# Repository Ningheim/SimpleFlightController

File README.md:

# SimpleFlightController

This is a USB-C powered 2-layer flight controller built around the STM32F722. It's 2S LiPo/Li-ion battery, a 6-axis IMU, a barometer, microSD logging, and two servo outputs.

## List of Materials

- MCU: STM32F722RET6
- IMU: ICM-20948 (SPI) — barometer: BME280 (I2C)
- Charger: BQ25887
- Power: TPS63070 buck-boost, LMR51430 buck
- microSD: 4-bit SD card slot
- J1/J3: servo/PWM headers
- J2: 2S battery screw terminal
- SW1 reset, SW2 boot, D1 status LED indicator
- 25MHz HSE + 32.768kHz LSE crystals
- Board: 50x55mm, 2-layer, KiCad 
- the hardware folder has the KiCad files. Run lcsc.py first to get parts KiCAD didn't have. This came from the hack club guide.

## Power architecture

```
2S Battery ----> TPS63070 ----> VSYS ----> LMR51430 ----> 3.3V rail

USB-C VBUS ----> BQ25887 Charger
```

## How To Make It Yourself

1. Run `lcsc.py` so the libraries resolve.
2. Open the .kicad_pro file in KiCad.
3. Export gerbers/drill/pick-and-place and send to JLCPCB for a quote.
4. Generate a BOM and assemble with a stencil, paste, and reflow.
5. Power up: 2S LIPO pack on the battery pad, `J2`.
6. Flash: hold `SW2`, reset with `SW1`, flash over `USB1`.

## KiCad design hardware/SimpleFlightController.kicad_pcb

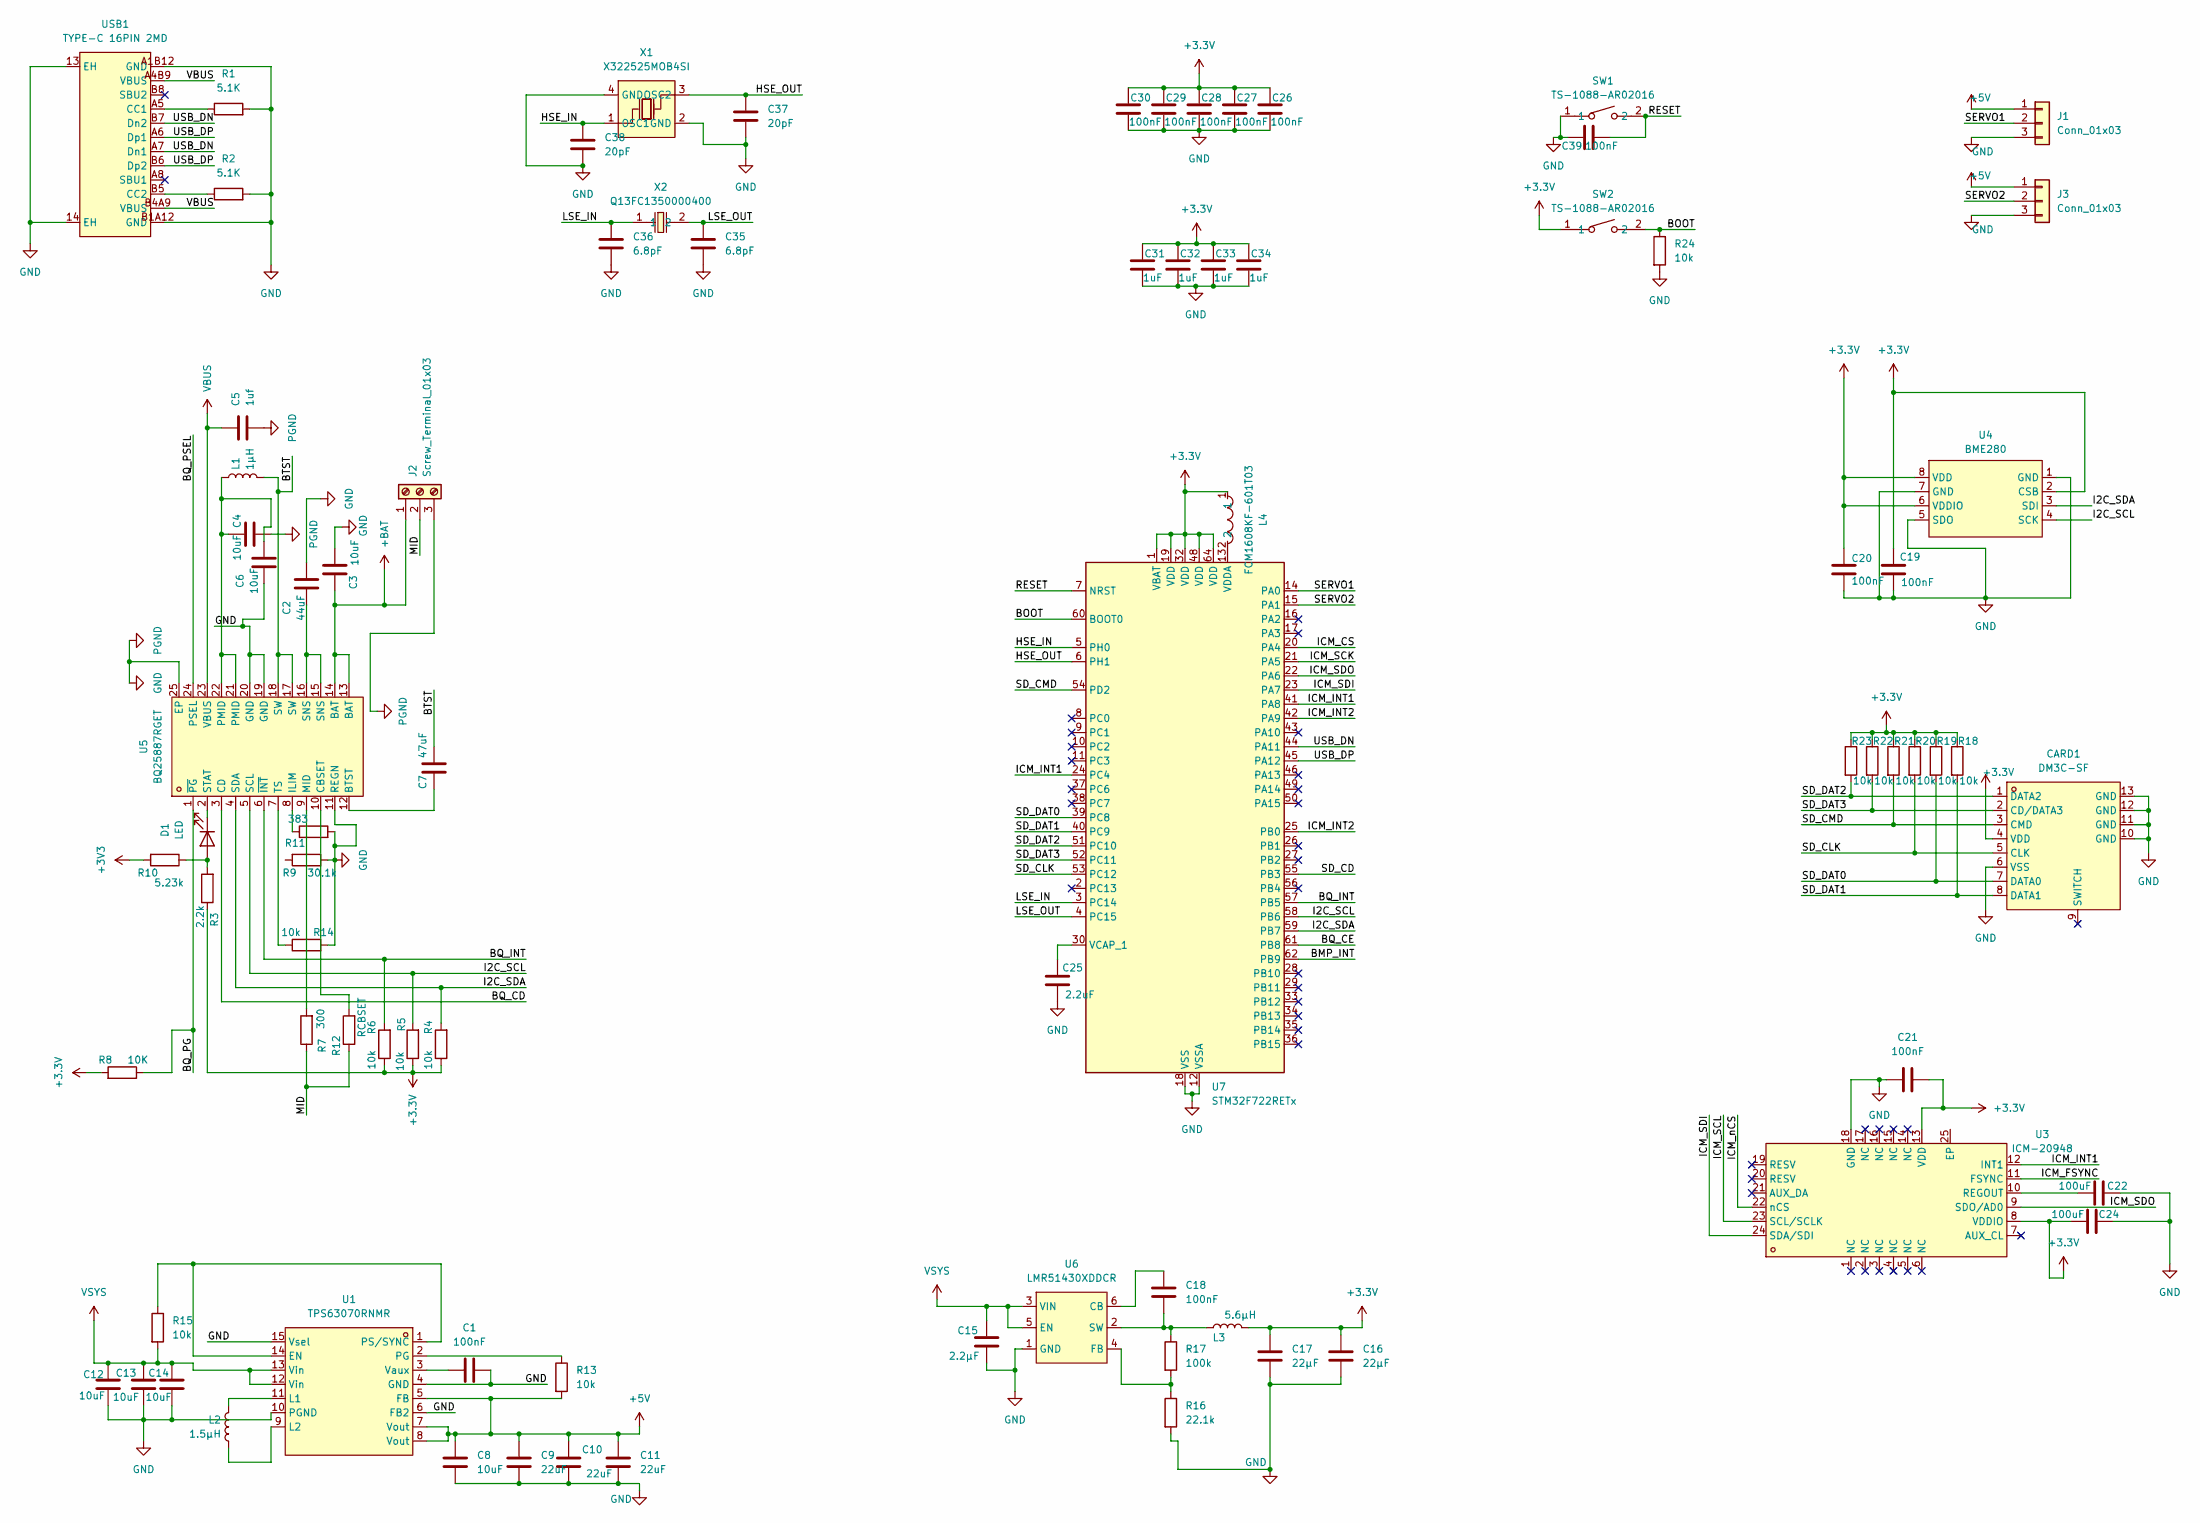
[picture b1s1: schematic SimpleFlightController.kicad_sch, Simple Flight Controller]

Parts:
C1, C18, C19, C20, C21, C26, C27, C28, C29, C30, C39: 100nF; C_0402_1005Metric
C2: 44uF; C_0805_2012Metric
C3, C4, C6, C8, C12, C13, C14: 10uF; C_0402_1005Metric
C5: 1uf; C_0402_1005Metric
C7: 47uF; C_0805_2012Metric
C9, C10, C11: 22uF; C_0805_2012Metric
C15: 2.2μF; C_0402_1005Metric
C16, C17: 22μF; C_0805_2012Metric
C22, C24: 100uF; C_0402_1005Metric
C25: 2.2uF; C_0402_1005Metric
C31, C32, C33, C34: 1uF; C_0402_1005Metric
C35, C36: 6.8pF; C_0402_1005Metric
C37, C38: 20pF; C_0402_1005Metric
CARD1: DM3C-SF; TF-SMD_DM3CS-SF; MPN DM3C-SF; LCSC Part C3177034
D1: LED; LED_0402_1005Metric
J1, J3: Conn_01x03; PinHeader_2x03_P2.54mm_Vertical
J2: Screw_Terminal_01x03; TerminalBlock_Xinya_XY308-2.54-3P_1x03_P2.54mm_Horizontal
L1: 1μH; L_1008_2520Metric
L2: 1.5μH; L_APV_ANR4012
L3: 5.6μH; L_1210_3225Metric
L4: FCM1608KF-601T03; L0603; MPN FCM1608KF-601T03; LCSC Part C141723
R1, R2: 5.1K; R_0201_0603Metric
R3: 2.2k; R_0201_0603Metric
R4, R5, R6, R13, R14, R15, R18, R19, R20, R21, R22, R23, R24: 10k; R_0201_0603Metric
R7: 300; R_0201_0603Metric
R8: 10K; R_0201_0603Metric
R9: 30.1k; R_0201_0603Metric
R10: 5.23k; R_0201_0603Metric
R11: 383; R_0201_0603Metric
R12: RCBSET; R_0201_0603Metric
R16: 22.1k; R_0201_0603Metric
R17: 100k; R_0201_0603Metric
SW1, SW2: TS-1088-AR02016; SW-SMD_L3.9-W3.0-P4.45; MPN TS-1088-AR02016; LCSC Part C720477
U1: TPS63070RNMR; VQFN-15_L3.0-W2.5-P0.50-BL; MPN TPS63070RNMR; LCSC Part C109322
U3: ICM-20948; QFN-24_L3.0-W3.0-P0.40-BL-EP; MPN ICM-20948; LCSC Part C726001
U4: BME280; LGA-8_BME280_BL; MPN BME280; LCSC Part C92489
U5: BQ25887RGET; VQFN-24_L4.0-W4.0-P0.50-TL-EP2.7; MPN BQ25887RGET; LCSC Part C2862617
U6: LMR51430XDDCR; SOT-23-6_L2.9-W1.6-P0.95-LS2.8-BL; MPN LMR51430XDDCR; LCSC Part C5185863
U7: STM32F722RETx; LQFP-64_10x10mm_P0.5mm
USB1: TYPE-C 16PIN 2MD; USB-C-SMD_TYPE-C-16PIN-2MD-073; MPN TYPE-C 16PIN 2MD(073); LCSC Part C2765186
X1: X322525MOB4SI; CRYSTAL-SMD_4P-L3.2-W2.5-BL; MPN X322525MOB4SI; LCSC Part C9006
X2: Q13FC1350000400; FC-135R_L3.2-W1.5; MPN Q13FC13500004; LCSC Part C32346

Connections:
+3.3V: C16.1, C17.1, C19.1, C20.1, C21.2, C24.1, C26.1, C27.1, C28.1, C29.1, C30.1, C31.1, C32.1, C33.1, C34.1, CARD1.4 (VDD), L3.2, L4.1, R3.1, R4.1, R5.1, R6.1, R8.2, R18.1, R19.1, R20.1, R21.1, R22.1, R23.1, SW2.1, U3.8 (VDDIO), U3.13 (VDD), U4.2 (CSB), U4.6 (VDDIO), U4.8 (VDD), U7.1 (VBAT), U7.19 (VDD), U7.32 (VDD), U7.48 (VDD), U7.64 (VDD)
+3V3: R10.2
+5V: C8.1, C9.1, C10.1, C11.1, J1.1, J3.1, R13.2, U1.5 (FB), U1.7 (Vout), U1.8 (Vout)
+BAT: C3.1, J2.1, U5.13 (BAT), U5.14 (BAT)
/BMP_INT: U7.62 (PB9)
/BOOT: R24.1, SW2.2, U7.60 (BOOT0)
/BQ_CD: U5.3 (CD)
/BQ_CE: U7.61 (PB8)
/BQ_INT: R6.2, U5.6 (~INT), U7.57 (PB5)
/BQ_PG: R8.1, U5.1 (~PG)
/BQ_PSEL: U5.24 (PSEL)
/BTST: C7.2, L1.2, U5.17 (SW), U5.18 (SW)
/HSE_IN: C38.1, U7.5 (PH0), X1.1 (OSC1)
/HSE_OUT: C37.1, U7.6 (PH1), X1.3 (OSC2)
/I2C_SCL: R5.2, U4.4 (SCK), U5.5 (SCL), U7.58 (PB6)
/I2C_SDA: R4.2, U4.3 (SDI), U5.4 (SDA), U7.59 (PB7)
/ICM_CS: U7.20 (PA4)
/ICM_FSYNC: U3.11 (FSYNC)
/ICM_INT1: U3.12 (INT1), U7.24 (PC4), U7.41 (PA8)
/ICM_INT2: U7.25 (PB0), U7.42 (PA9)
/ICM_SCK: U7.21 (PA5)
/ICM_SCL: U3.23 (SCL/SCLK)
/ICM_SDI: U3.24 (SDA/SDI), U7.23 (PA7)
/ICM_SDO: U3.9 (SDO/AD0), U7.22 (PA6)
/ICM_nCS: U3.22 (nCS)
/LSE_IN: C36.1, U7.3 (PC14), X2.1
/LSE_OUT: C35.1, U7.4 (PC15), X2.2
/MID: J2.2, R7.1, R12.1
/RESET: C39.2, SW1.2, U7.7 (NRST)
/SD_CD: U7.55 (PB3)
/SD_CLK: CARD1.5 (CLK), R20.2, U7.53 (PC12)
/SD_CMD: CARD1.3 (CMD), R21.2, U7.54 (PD2)
/SD_DAT0: CARD1.7 (DATA0), R19.2, U7.39 (PC8)
/SD_DAT1: CARD1.8 (DATA1), R18.2, U7.40 (PC9)
/SD_DAT2: CARD1.1 (DATA2), R23.2, U7.51 (PC10)
/SD_DAT3: CARD1.2 (CD/DATA3), R22.2, U7.52 (PC11)
/SERVO1: J1.2, U7.14 (PA0)
/SERVO2: J3.2, U7.15 (PA1)
/USB_DN: U7.44 (PA11), USB1.A7 (Dn1), USB1.B7 (Dn2)
/USB_DP: U7.45 (PA12), USB1.A6 (Dp1), USB1.B6 (Dp2)
GND: C1.1, C2.2, C3.2, C4.2, C5.2, C6.1, C8.2, C9.2, C10.2, C11.2, C12.2, C13.2, C14.2, C15.2, C16.2, C17.2, C19.2, C20.2, C21.1, C22.2, C24.2, C25.2, C26.2, C27.2, C28.2, C29.2, C30.2, C31.2, C32.2, C33.2, C34.2, C35.2, C36.2, C37.2, C38.2, C39.1, CARD1.6 (VSS), CARD1.10 (GND), CARD1.11 (GND), CARD1.12 (GND), CARD1.13 (GND), J1.3, J2.3, J3.3, R1.2, R2.2, R9.1, R11.2, R14.2, R16.2, R24.2, SW1.1, U1.4 (GND), U1.6 (FB2), U1.10 (PGND), U1.15 (Vsel), U3.18 (GND), U4.1 (GND), U4.5 (SDO), U4.7 (GND), U5.11 (REGN), U5.19 (GND), U5.20 (GND), U5.25 (EP), U6.1 (GND), U7.12 (VSSA), U7.18 (VSS), U7.31 (VSS), U7.47 (VSS), U7.63 (VSS), USB1.13 (EH), USB1.14 (EH), USB1.A1B12 (GND), USB1.B1A12 (GND), X1.2 (GND), X1.4 (GND)
unnamed: C2.1, U5.15 (SNS), U5.16 (SNS)
unnamed: C4.1, C6.2, L1.1, U5.21 (PMID), U5.22 (PMID)
unnamed: D1.2 (A), R3.2, R10.1
unnamed: D1.1 (K), U5.2 (STAT)
unnamed: R15.1, U1.1 (PS/SYNC), U1.14 (EN)
unnamed: L2.1, U1.11 (L1)
unnamed: L2.2, U1.9 (L2)
unnamed: R13.1, U1.2 (PG)
unnamed: C1.2, U1.3 (Vaux)
unnamed: C22.1, U3.10 (REGOUT)
unnamed: C7.1, U5.12 (BTST)
unnamed: R12.2, U5.10 (CBSET)
unnamed: R11.1, U5.8 (ILIM)
unnamed: R7.2, U5.9 (MID)
unnamed: R14.1, U5.7 (TS)
unnamed: C18.1, U6.6 (CB)
unnamed: R16.1, R17.2, U6.4 (FB)
unnamed: C18.2, L3.1, R17.1, U6.2 (SW)
unnamed: C25.1, U7.30 (VCAP_1)
unnamed: L4.2, U7.13 (VDDA)
unnamed: R1.1, USB1.A5 (CC1)
unnamed: R2.1, USB1.B5 (CC2)
VBUS: C5.1, U5.23 (VBUS), USB1.A4B9 (VBUS), USB1.B4A9 (VBUS)
VSYS: C12.1, C13.1, C14.1, C15.1, R15.2, U1.12 (Vin), U1.13 (Vin), U6.3 (VIN), U6.5 (EN)

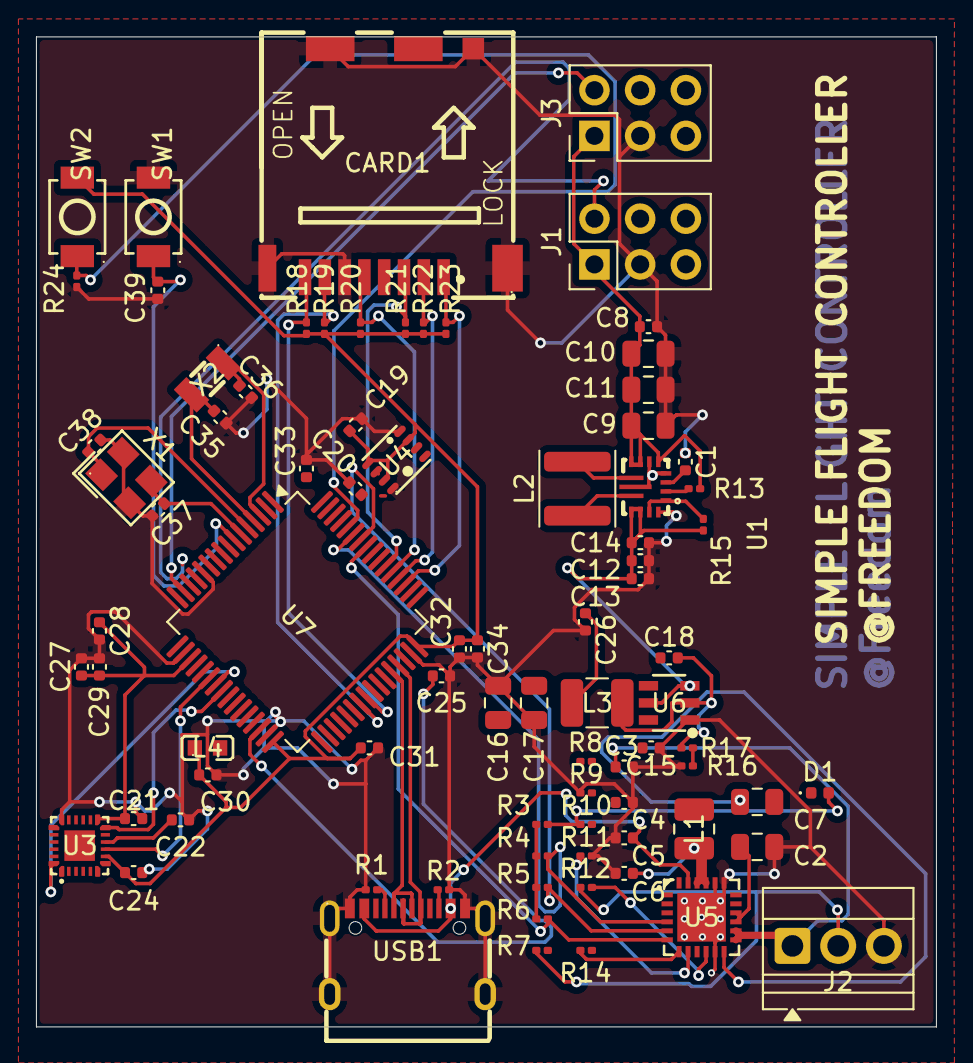
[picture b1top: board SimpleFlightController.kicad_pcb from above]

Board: 2 copper layers, 50.0 x 55.0 mm, 82 parts (0 on the bottom side), 54 nets.

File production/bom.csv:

Designator,Footprint,Quantity,Value,LCSC Part #
"C1, C18, C19, C20, C21, C26, C27, C28, C29, C30, C39",0402,11,100nF,
"C10, C11, C9",0805,3,22uF,
"C12, C13, C14, C3, C4, C6, C8",0402,7,10uF,
C15,0402,1,2.2μF,
"C16, C17",0805,2,22μF,
C2,0805,1,44uF,
"C22, C24",0402,2,100uF,
C25,0402,1,2.2uF,
"C31, C32, C33, C34, C5",0402,5,1uF,
"C35, C36",0402,2,6.8pF,
"C37, C38",0402,2,20pF,
C7,0805,1,47uF,
CARD1,TF-SMD_DM3CS-SF,1,DM3C-SF,C3177034
D1,0402,1,LED,
"J1, J3",PinHeader_2x03_P2.54mm_Vertical,2,Conn_01x03,
J2,TerminalBlock_Xinya_XY308-2.54-3P_1x03_P2.54mm_Horizontal,1,Screw_Terminal_01x03,
L1,1008,1,1μH,
L2,L_APV_ANR4012,1,1.5μH,
L3,1210,1,5.6μH,
L4,L0603,1,FCM1608KF-601T03,C141723
"R1, R2",0201,2,5.1K,
R10,0201,1,5.23k,
R11,0201,1,383,
R12,0201,1,RCBSET,
"R13, R14, R15, R18, R19, R20, R21, R22, R23, R24, R4, R5, R6, R8",0201,14,10k,
R16,0201,1,22.1k,
R17,0201,1,100k,
R3,0201,1,2.2k,
R7,0201,1,300,
R9,0201,1,30.1k,
"SW1, SW2",SW-SMD_L3.9-W3.0-P4.45,2,TS-1088-AR02016,C720477
U1,VQFN-15_L3.0-W2.5-P0.50-BL,1,TPS63070RNMR,C109322
U3,QFN-24_L3.0-W3.0-P0.40-BL-EP,1,ICM-20948,C726001
U4,LGA-8_BME280_BL,1,BME280,C92489
U5,VQFN-24_L4.0-W4.0-P0.50-TL-EP2.7,1,BQ25887RGET,C2862617
U6,SOT-23-6_L2.9-W1.6-P0.95-LS2.8-BL,1,LMR51430XDDCR,C5185863
U7,LQFP-64_10x10mm_P0.5mm,1,STM32F722RETx,
USB1,USB-C-SMD_TYPE-C-16PIN-2MD-073,1,TYPE-C 16PIN 2MD,C2765186
X1,CRYSTAL-SMD_4P-L3.2-W2.5-BL,1,X322525MOB4SI,C9006
X2,FC-135R_L3.2-W1.5,1,Q13FC1350000400,C32346

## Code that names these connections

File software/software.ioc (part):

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Mcu.Name=STM32F722R(C-E)Tx
Mcu.Package=LQFP64
Mcu.UserName=STM32F722RETx
PA0-WKUP.Signal=S_TIM2_CH1_ETR
PA1.Signal=S_TIM2_CH2
PA11.Mode=Host_Only
PA11.Signal=USB_OTG_FS_DM
PA12.Mode=Host_Only
PA12.Signal=USB_OTG_FS_DP
PA4.Mode=NSS_Signal_Hard_Output
PA4.Signal=SPI1_NSS
PA5.Mode=Full_Duplex_Master
PA5.Signal=SPI1_SCK
PA6.Mode=Full_Duplex_Master
PA6.Signal=SPI1_MISO
PA7.Mode=Full_Duplex_Master
PA7.Signal=SPI1_MOSI
PB0.Signal=GPXTI0
PB3.Signal=GPIO_Input
PB5.Signal=GPXTI5
PB6.Mode=I2C
PB6.Signal=I2C1_SCL
PB7.Mode=I2C
PB7.Signal=I2C1_SDA
PB8.Signal=GPIO_Output
PB9.Signal=GPXTI9
PC10.Mode=SD_4_bits_Wide_bus
PC10.Signal=SDMMC1_D2
PC11.Mode=SD_4_bits_Wide_bus
PC11.Signal=SDMMC1_D3
PC12.Mode=SD_4_bits_Wide_bus
PC12.Signal=SDMMC1_CK
PC14-OSC32_IN.Mode=LSE-External-Oscillator
PC14-OSC32_IN.Signal=RCC_OSC32_IN
PC15-OSC32_OUT.Mode=LSE-External-Oscillator
PC15-OSC32_OUT.Signal=RCC_OSC32_OUT
PC4.Signal=GPXTI4
PC8.Mode=SD_4_bits_Wide_bus
PC8.Signal=SDMMC1_D0
PC9.Mode=SD_4_bits_Wide_bus
PC9.Signal=SDMMC1_D1
PD2.Mode=SD_4_bits_Wide_bus
PD2.Signal=SDMMC1_CMD
PH0-OSC_IN.Mode=HSE-External-Oscillator
PH0-OSC_IN.Signal=RCC_OSC_IN
PH1-OSC_OUT.Mode=HSE-External-Oscillator
PH1-OSC_OUT.Signal=RCC_OSC_OUT
RCC.HSE_VALUE=25000000
board=custom

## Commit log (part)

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2026-05-21 Battery Charger 80% Done
    I ended up finishing wiring all the pins except for the battery related ones, I'll finish those tomorrow and I'll move on to the sensors.
2026-05-23 5/22/2026: Finished Regulator, Sensor, and Tracker
    Everything went smoothly, using the datasheets for so long has given me a better understanding on what each symbol means/does.
2026-05-26 Finished Schematic
2026-05-28 PCB Footprints
2026-06-07 PCB Routing
2026-06-10 PCB Layout Almost Final
